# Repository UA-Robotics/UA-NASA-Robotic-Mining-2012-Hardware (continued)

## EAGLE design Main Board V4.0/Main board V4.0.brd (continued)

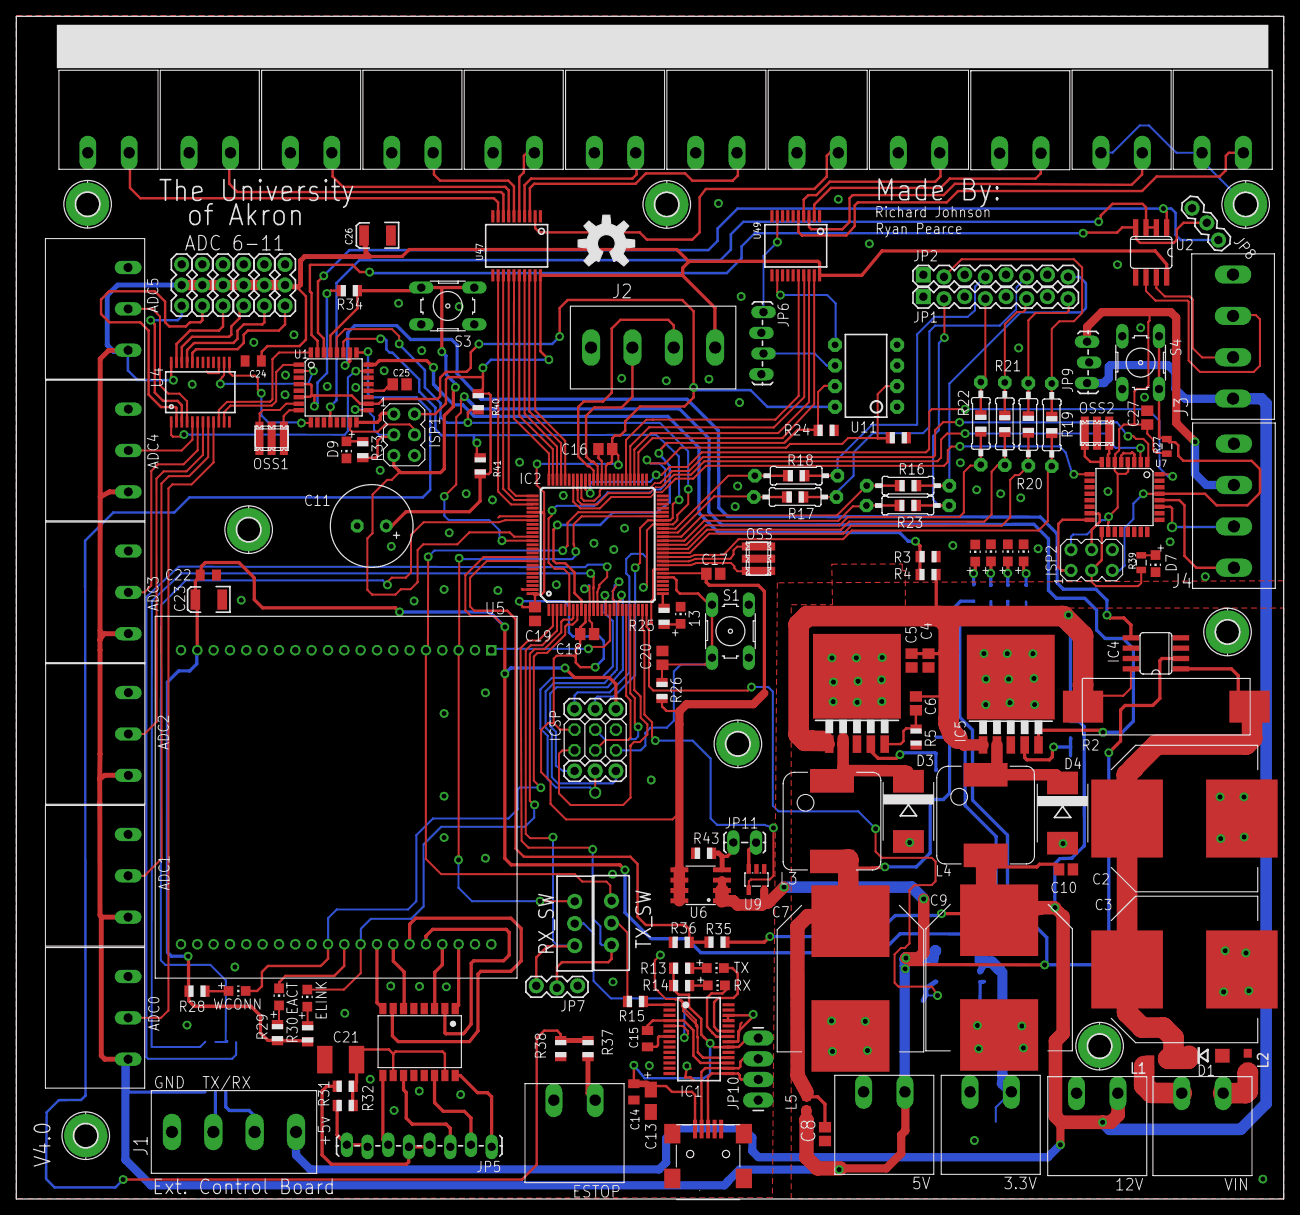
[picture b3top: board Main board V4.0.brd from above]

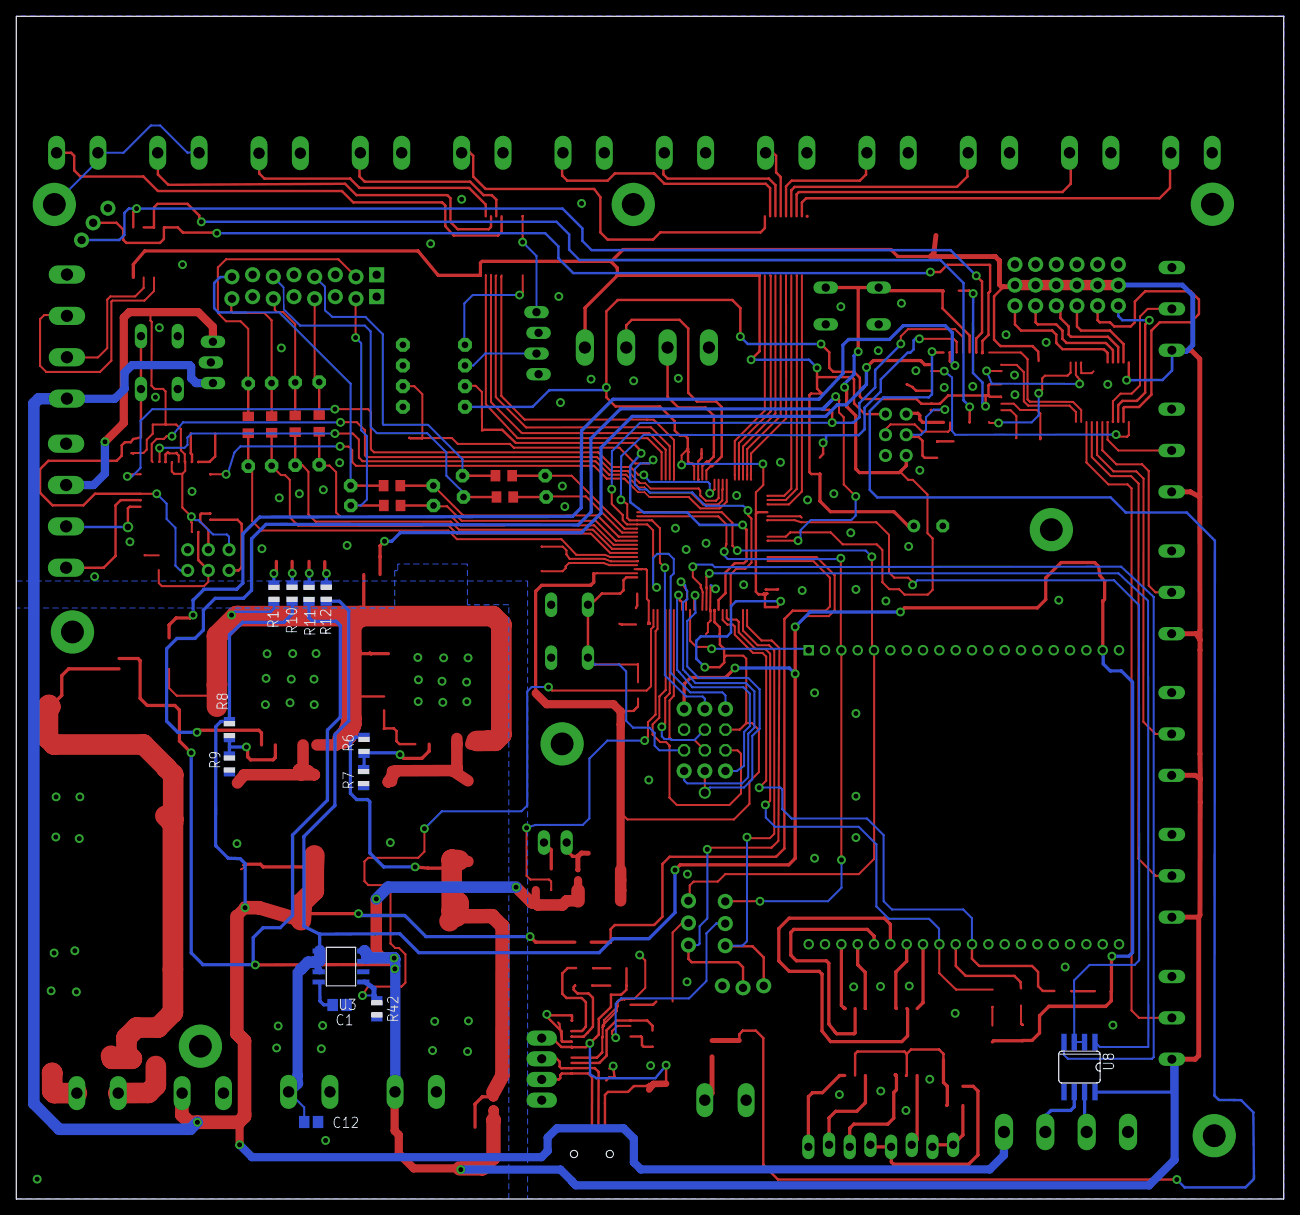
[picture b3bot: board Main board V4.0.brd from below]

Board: 2 copper layers, 155.7 x 145.3 mm, 174 parts (13 on the bottom side), 174 nets.

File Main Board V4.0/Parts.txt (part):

Partlist

Exported from Main board V4.0.sch at 3/19/2012 11:14:36 PM

EAGLE Version 6.0.0 Copyright (c) 1988-2011 CadSoft

Assembly variant: 

Part     Value              Device             Package            Library      Sheet

3.3V     EUROMAG-2          EUROMAG-2          M2                 RJ's_parts   2
5V       EUROMAG-2          EUROMAG-2          M2                 RJ's_parts   2
12V      EUROMAG-2          EUROMAG-2          M2                 RJ's_parts   2
13                          LEDCHIP-LED0805    CHIP-LED0805       adafruit     2
ADC0     EUROMAG-390DEG     EUROMAG-390DEG     M3                 RJ's_parts   4
ADC1     EUROMAG-390DEG     EUROMAG-390DEG     M3                 RJ's_parts   4
ADC2     EUROMAG-390DEG     EUROMAG-390DEG     M3                 RJ's_parts   4
ADC3     EUROMAG-390DEG     EUROMAG-390DEG     M3                 RJ's_parts   4
ADC4     EUROMAG-390DEG     EUROMAG-390DEG     M3                 RJ's_parts   4
ADC5     EUROMAG-390DEG     EUROMAG-390DEG     M3                 RJ's_parts   4
ADC6                        M03PTH             1X03               SparkFun     4
ADC7                        M03PTH             1X03               SparkFun     4
ADC8                        M03PTH             1X03               SparkFun     4
ADC9                        M03PTH             1X03               SparkFun     4
ADC10                       M03PTH             1X03               SparkFun     4
ADC11                       M03PTH             1X03               SparkFun     4
C2       1200uF/50v         CAP_CAN1           CAN_18MM           NASA_LIB     1
C3       1200uF/50v         CAP_CAN1           CAN_18MM           NASA_LIB     1
C4       1uf/50v            C-USC0805          C0805              adafruit     1
C5       1uf/50v            C-USC0805          C0805              adafruit     1
C6       0.1uF/50v          C-USC0805          C0805              adafruit     1
C7       1000uF/25v         CAP_CAN1           CAN_18MM           NASA_LIB     1
C8       1uF/50v            C-USC0805          C0805              adafruit     1
C9       1000uF/25v         CAP_CAN1           CAN_18MM           NASA_LIB     1
C10      1uF/50v            C-USC0805          C0805              adafruit     1
C11      10uF/16v           CPOL-USE3.5-10     E3,5-10            adafruit     1
C12      10uf/16v           C-USC0805          C0805              adafruit     1
C13      10uF               CPOL-USA/3216-18R  A/3216-18R         adafruit     3
C14      0.1uF              C-USC0805K         C0805K             adafruit     3
C15      0.1uF              C-USC0805K         C0805K             adafruit     3
C16      100n               C-USC0805          C0805              adafruit     2
C17      100n               C-USC0805          C0805              adafruit     2
C18      100n               C-USC0805          C0805              adafruit     2
C19      100n               C-USC0805          C0805              adafruit     2
C20      22p                C-USC0805          C0805              adafruit     2
C21                         C-USC1812          C1812              adafruit     3
C22      0.1uf              C-USC0805K         C0805K             adafruit     3
C23      10uf               CAP_POL3528        EIA3528            SparkFun     3
C24      0.1uF              C-USC0805K         C0805K             adafruit     3
C25      0.1uF              C-USC0805          C0805              adafruit     3
C26      10uF               CAP_POL3528        EIA3528            SparkFun     3
C27      0.1uF              C-USC0805          C0805              adafruit     2
CN1      MINIB              USBMINIB           USB-MINIB          adafruit     3
D1       TVS                TVS                DO-214AC           NASA_LIB     1
D2       Vin                LEDCHIP-LED0805    CHIP-LED0805       adafruit     1
D3                          DIODE-SMC          SMC                diode        1
D4                          DIODE-SMC          SMC                diode        1
D5       5v                 LEDCHIP-LED0805    CHIP-LED0805       adafruit     2
D6       3.3v               LEDCHIP-LED0805    CHIP-LED0805       adafruit     2
D7                          LEDCHIP-LED0805    CHIP-LED0805       adafruit     2
D8       12                 LEDCHIP-LED0805    CHIP-LED0805       adafruit     2
D9                          LEDCHIP-LED0805    CHIP-LED0805       adafruit     3
EACT                        LEDCHIP-LED0805    CHIP-LED0805       adafruit     3
ELINK                       LEDCHIP-LED0805    CHIP-LED0805       adafruit     3
ESTOP    EUROMAG-2          EUROMAG-2          M2                 RJ's_parts   1
H2       MOUNT-PAD-ROUND2.8 MOUNT-PAD-ROUND2.8 2,8-PAD            holes        4
H3       MOUNT-PAD-ROUND2.8 MOUNT-PAD-ROUND2.8 2,8-PAD            holes        4
H4       MOUNT-PAD-ROUND2.8 MOUNT-PAD-ROUND2.8 2,8-PAD            holes        4
H5       MOUNT-PAD-ROUND2.8 MOUNT-PAD-ROUND2.8 2,8-PAD            holes        4
H6       MOUNT-PAD-ROUND2.8 MOUNT-PAD-ROUND2.8 2,8-PAD            holes        4
H7       MOUNT-PAD-ROUND2.8 MOUNT-PAD-ROUND2.8 2,8-PAD            holes        4
H8       MOUNT-PAD-ROUND2.8 MOUNT-PAD-ROUND2.8 2,8-PAD            holes        4
H10      MOUNT-PAD-ROUND2.8 MOUNT-PAD-ROUND2.8 2,8-PAD            holes        4
IC1      FT232RL            FT232RL            SSOP28             ftdichip     3
IC2      ATMEGA1280-16AU    ATMEGA1280-16AU    TQFP100            atmel-2005   2
IC3      LM2576             LM2576             TO-263-5           NASA_LIB     1
IC4      MAX4080            MAX4080            SO08               RJ's parts   1
IC5      LM2576             LM2576             TO-263-5           NASA_LIB     1
ICSP     ICSP               PINHD-2X3          2X03               pinhead      2
ISP1     AVRISP-6           AVRISP-6           AVRISP             adafruit     3
ISP2     AVRISP-6           AVRISP-6           AVRISP             adafruit     2
J1       EUROMAG-4          EUROMAG-4          M4                 RJ's_parts   2
J2       EUROMAG-4          EUROMAG-4          M4                 RJ's_parts   2
J3       EUROMAG-4          EUROMAG-4          M4                 NASA_LIB     3
J4       I2C LED            EUROMAG-4          M4                 NASA_LIB     2
J19      EUROMAG-2          EUROMAG-2          M2                 RJ's_parts   4
J20      EUROMAG-2          EUROMAG-2          M2                 RJ's_parts   4
J21      EUROMAG-2          EUROMAG-2          M2                 RJ's_parts   4
J22      EUROMAG-2          EUROMAG-2          M2                 RJ's_parts   4
J23      EUROMAG-2          EUROMAG-2          M2                 RJ's_parts   4
J24      EUROMAG-2          EUROMAG-2          M2                 RJ's_parts   4
J25      EUROMAG-2          EUROMAG-2          M2                 RJ's_parts   4
J26      EUROMAG-2          EUROMAG-2          M2                 RJ's_parts   4
J27      EUROMAG-2          EUROMAG-2          M2                 RJ's_parts   4
J28      EUROMAG-2          EUROMAG-2          M2                 RJ's_parts   4
J29      EUROMAG-2          EUROMAG-2          M2                 RJ's_parts   4
J30      EUROMAG-2          EUROMAG-2          M2                 RJ's_parts   4
JP1                         M08LOCK            1X08_LOCK          SparkFun     4
JP2                         M08LOCK            1X08_LOCK          SparkFun     4
JP3                         M03PTH             1X03               SparkFun     2
JP4                         M03PTH             1X03               SparkFun     2
JP5                         M08LOCK_LONGPADS   1X08_LOCK_LONGPADS SparkFun     3
JP6                         M04LOCK_LONGPADS   1X04_LOCK_LONGPADS SparkFun     2
JP7                         M03LOCK            1X03_LOCK          SparkFun     2
JP8                         M03LOCK            1X03_LOCK          SparkFun     3
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
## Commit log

2015-08-14 Initial commit of the hardware schematics.
